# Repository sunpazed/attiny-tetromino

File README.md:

# attiny-tetromino 

<center></center>

This is my second-ever PCB, an Arduino Tetris game based around a attiny85. Most of the code was inspired by this hack https://github.com/jfoucher/attiny-tetris/ — however I made a number of modern modifications to Tetris (7-bag randomiser, DAS, debounce, NES speed improvements, new level and line system, new fonts). 

I started with a breadboard and then thought I'd try my hand at designing a PCB in Kicad. Here's [version 1](https://www.reddit.com/r/arduino/comments/1eph7te/my_first_pcb_an_arduino_attiny85_handheld/) and this project is version 2. Please excuse my poor hand soldering, as I'm only just beginning!

The game is quite small, at 50x44mm it's easily pocketable. The side profile is only 14mm, and could be make thinner by using a smaller battery holder.

<center></center>

## How to build your own

### Part list

The parts are relatively inexpensive, with the entire BOM and board costing less than $10 in total. To accomodate easier soldering I've selected larger surface mount components where possible, and the pads on the board are also wider.

- 1x attiny85-20su
- 1x SDD1306 monochrome OLED (128x32 pixels)
- 1x Mini 7-pin SMD toggle slide switch, [SPDT MSK-12C02](https://www.ckswitches.com/media/1424/pcm.pdf) 
- 4x SMD micro-switch 6x6x5mm
- 1x 470k SMD resistor (2512 size)
- 1x battery holder CR2032, [Keystone 1060](https://www.ckswitches.com/media/1424/pcm.pdf)

### Make the PCB

Order a PCB using the gerber files within the `pcb/fabrication` folder — simply zip this up and process the files through your favourite prototyping fab. The source also includes the Kicad project if you'd like to modify the PCB, components, or even just the silkscreen graphics.

<center></center>

### Programming the board

The board includes 6 programming pads directly connected to the attiny. You can see them here on the right-hand side of the rear of the pcb; 

<center></center>

These can be easily connected using a SOP16 programming clip for SOIC16 chips. Only the top section of the clip is used, and is mapped to GND, RST, PB0, PB1, PB3, and VCC. Connect the programming clip to your programming device or Arduino using DuPont jumper wires — learn more at [SOICBite](https://github.com/SimonMerrett/SOICbite)

Once the board is connected, load up the Arduino IDE and test the connection by burning the bootloader to the attiny. The bootloader configuration is defined within the `attiny_tetromino.ino` project.

If the bootloader completes without issue, you can now compile and upload the `attiny_tetromino.ino` project to your board. Pop in a CR2032 battery and enjoy playing!

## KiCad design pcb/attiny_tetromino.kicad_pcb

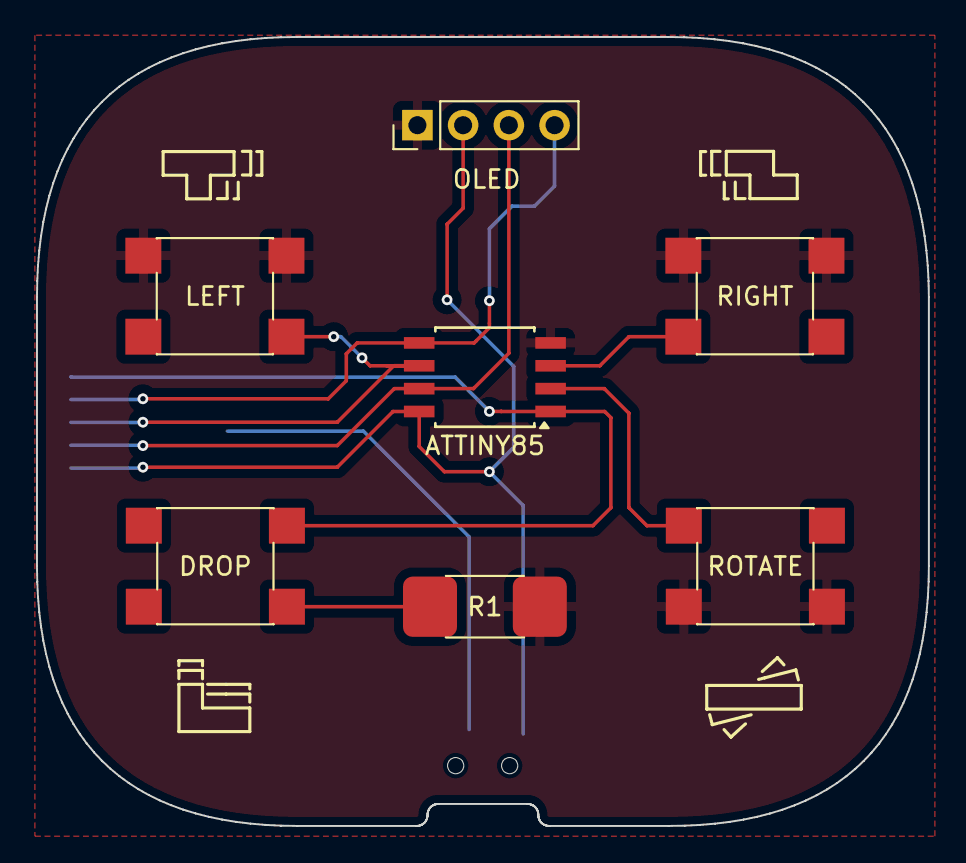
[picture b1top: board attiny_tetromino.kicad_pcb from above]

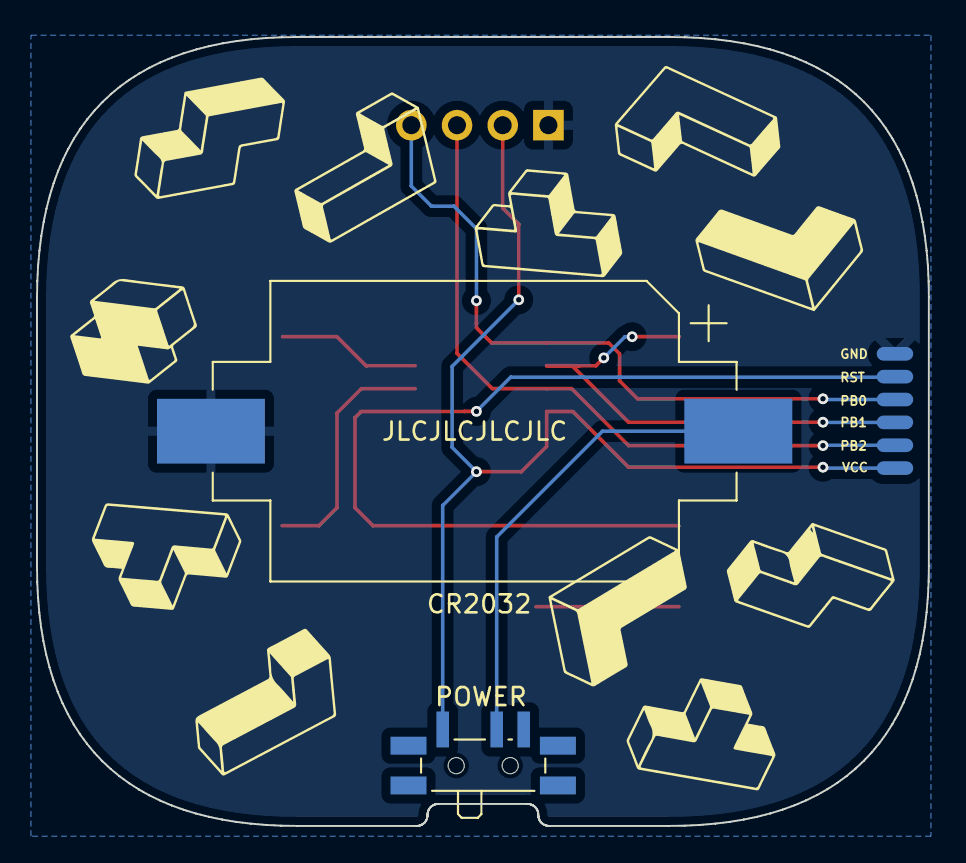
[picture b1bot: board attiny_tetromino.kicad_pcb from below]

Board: 2 copper layers, 49.5 x 43.8 mm, 10 parts (3 on the bottom side), 10 nets.

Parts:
ATTINY85: ATtiny85-20S; SOIC-8W_5.3x5.3mm_P1.27mm
CR2032: Battery_Cell; BatteryHolder_Keystone_1060_1x2032
DROP: SW_Push; SW_Push_1P1T_NO_6x6mm_H9.5mm
J1: Conn_01x06_Pin; SOICBite_16
LEFT: SW_Push; SW_Push_1P1T_NO_6x6mm_H9.5mm
OLED: Conn_01x04_Pin; PinHeader_1x04_P2.54mm_Vertical
POWER: SW_SPDT; SW_SPDT_PCM12
R1: 470k; R_2512_6332Metric_Pad1.40x3.35mm_HandSolder
RIGHT: SW_Push; SW_Push_1P1T_NO_6x6mm_H9.5mm
ROTATE: SW_Push; SW_Push_1P1T_NO_6x6mm_H9.5mm

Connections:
GND: ATTINY85.4 (GND), CR2032.2 (-), J1.1, LEFT.2, OLED.1, R1.2, RIGHT.2, ROTATE.2
unnamed: CR2032.1 (+), POWER.2 (B)
unnamed: DROP.2, R1.1
unnamed: ATTINY85.1 (~RESET/PB5), DROP.1, J1.2
unnamed: ATTINY85.5 (AREF/PB0), J1.3, OLED.4
unnamed: ATTINY85.6 (PB1), J1.4, LEFT.1
unnamed: ATTINY85.7 (PB2), J1.5, OLED.3
unnamed: ATTINY85.2 (XTAL1/PB3), ROTATE.1
unnamed: ATTINY85.3 (XTAL2/PB4), RIGHT.1
VCC: ATTINY85.8 (VCC), J1.6, OLED.2, POWER.1 (A)

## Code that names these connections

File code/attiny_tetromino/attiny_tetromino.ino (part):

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// pins of attiny85 w/ basic schematic
//
//  R470k + DROP BTN    RST  -|o     |-  Vcc                CR2023 (3v)
//  ROTATE BTN          PB3  -|      |-  PB2 (SCK/SCL)      OLED SCL
//  LEFT BTN            PB4  -|      |-  PB1 (MISO)         RIGHT BUTTON 
//                      GND  -|______|-  PB0 (MOSI/SDA)     OLED SDA
// 
// Bootloader configuration;
// - B.O.D. Disabled
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const uint8_t SCREEN_WIDTH = 16;
const uint8_t SCREEN_HEIGHT = 24;
const uint8_t EEPROM_ADDR = 4;
const uint8_t PIN_LEFT = PB4;
const uint8_t PIN_RIGHT = PB1;
const uint8_t PIN_ROTATE = PB3;
const uint8_t LEVEL_DELAY = 28;
const uint8_t TETROMINOES_BAG_SIZE = 7;

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
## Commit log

2024-09-08 added a license
2024-09-08 Rename device-side.JPG to device-side.jpg
2024-09-08 updated images
2024-09-09 We can get a better compile time optimization by using const instead of the preprocessor #define
